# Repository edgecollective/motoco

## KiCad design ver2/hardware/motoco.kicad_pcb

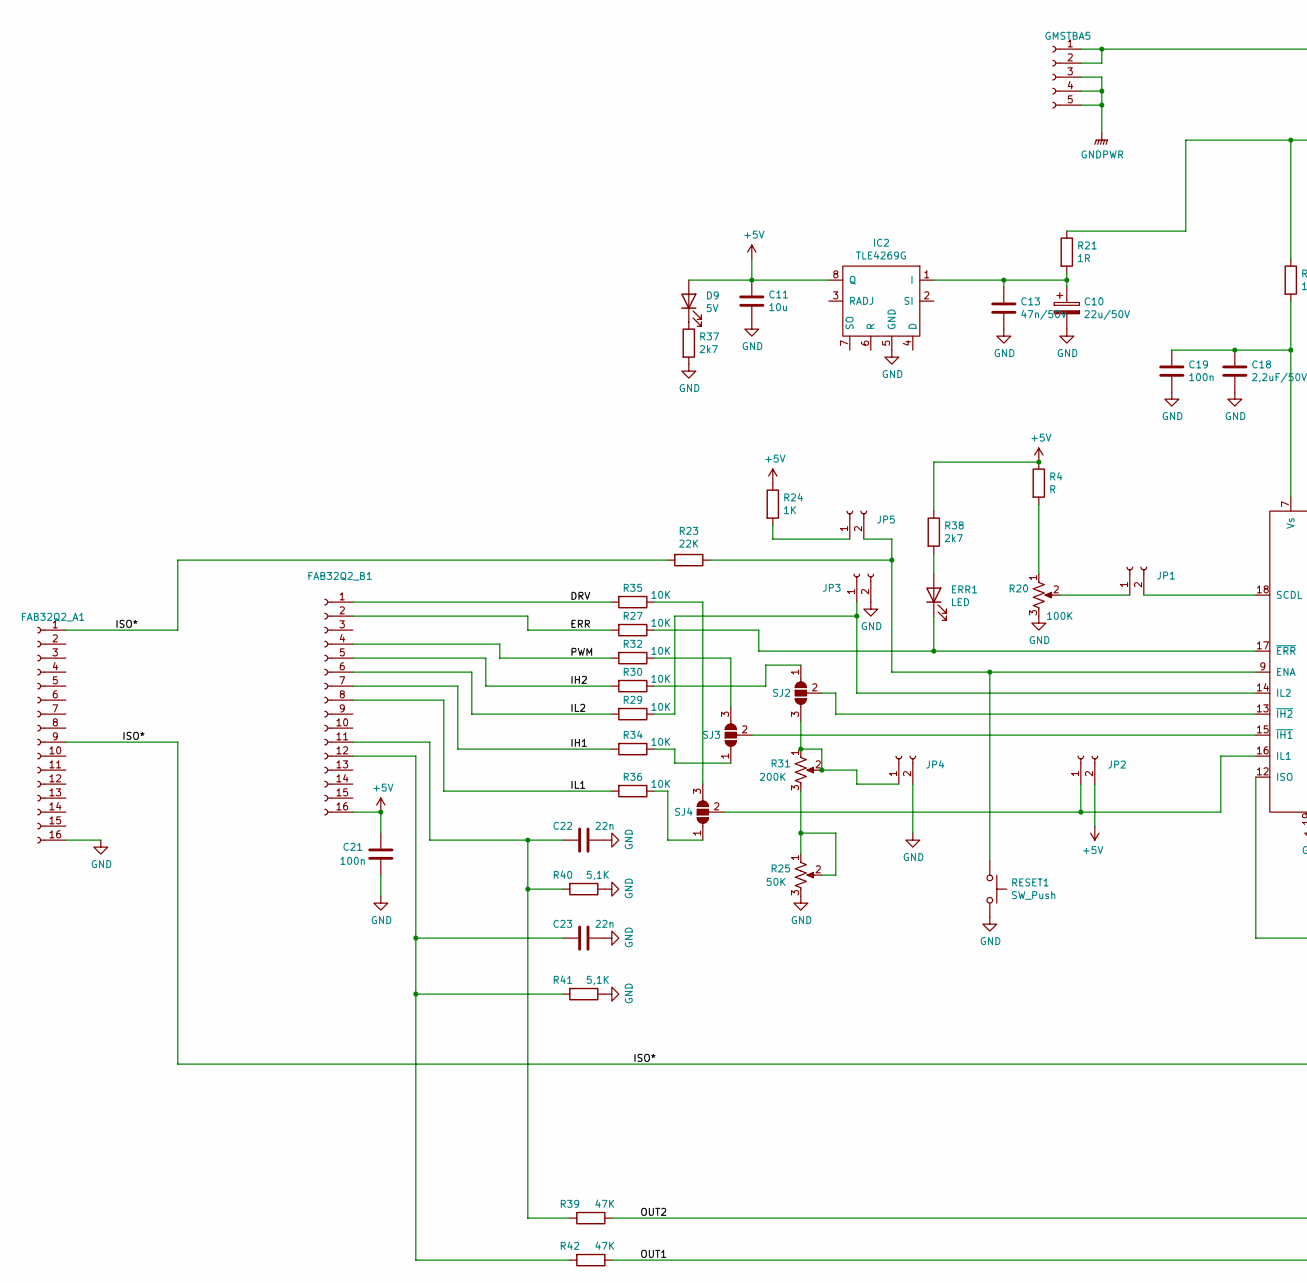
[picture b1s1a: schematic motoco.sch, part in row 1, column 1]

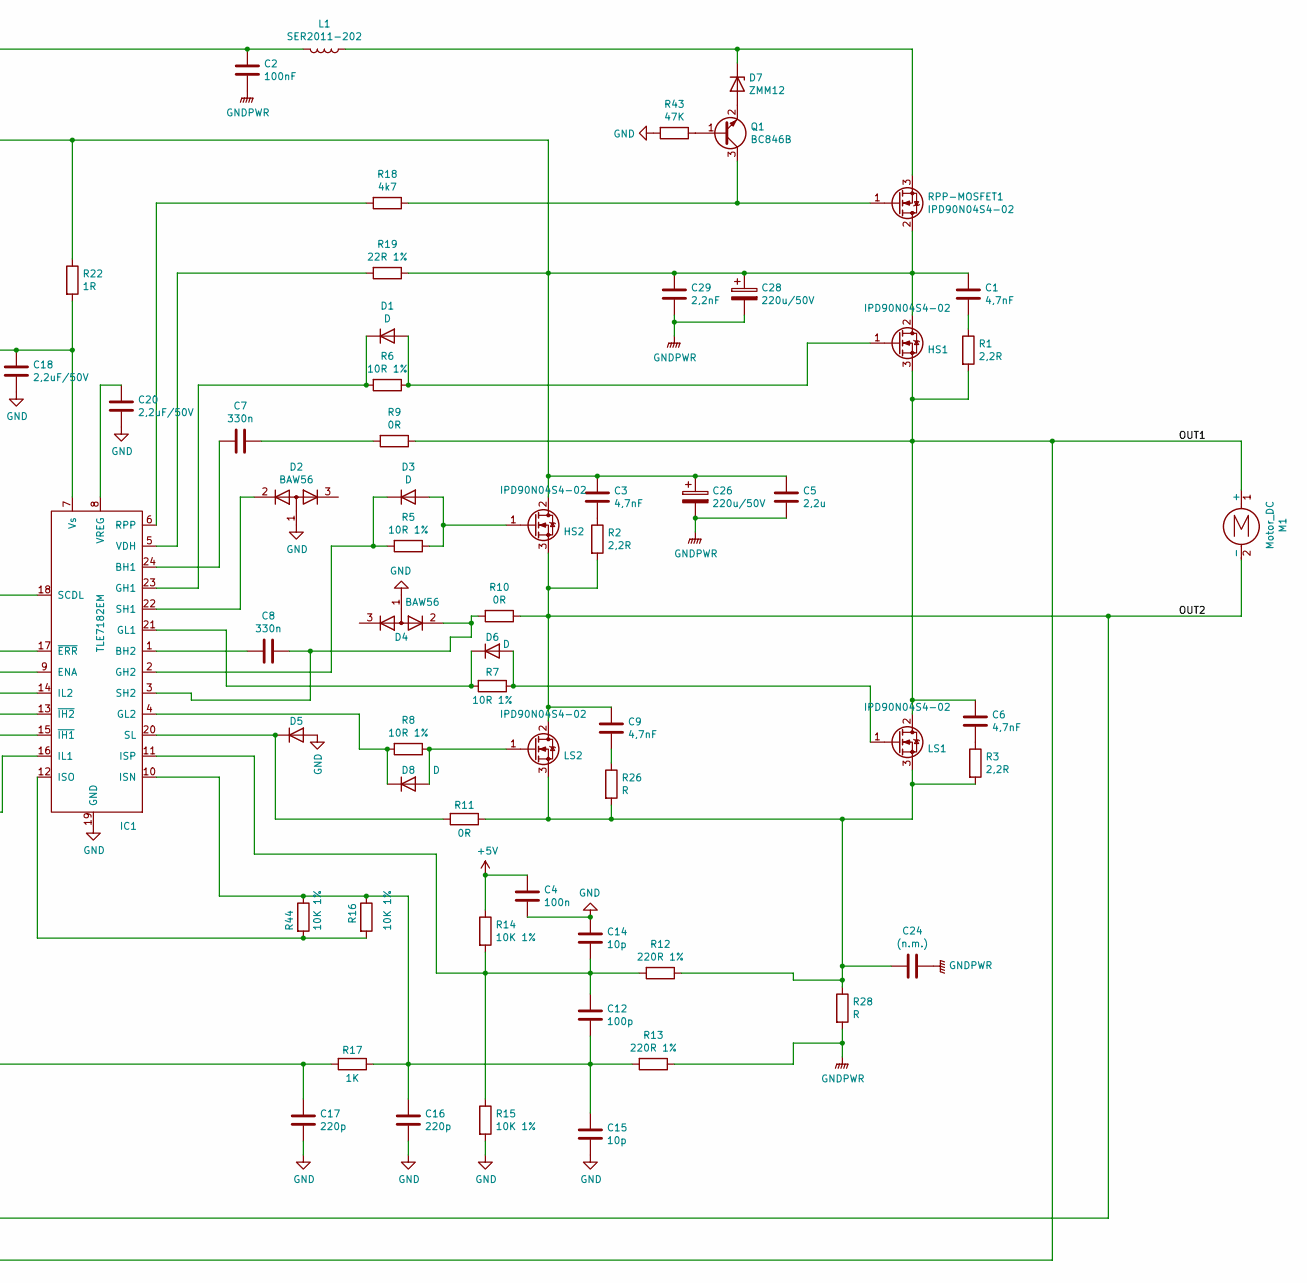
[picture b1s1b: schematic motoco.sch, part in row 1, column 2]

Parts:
C1, C3, C6, C9: 4,7nF; C_0603_1608Metric_Pad1.05x0.95mm_HandSolder
C2: 100nF; C_0603_1608Metric_Pad1.05x0.95mm_HandSolder
C4, C19, C21: 100n; C_0603_1608Metric_Pad1.05x0.95mm_HandSolder
C5: 2,2u; C_1210_3225Metric_Pad1.42x2.65mm_HandSolder
C7, C8: 330n; C_0603_1608Metric_Pad1.05x0.95mm_HandSolder
C10: 22u/50V; CP_Radial_D5.0mm_P2.00mm
C11: 10u; C_0603_1608Metric_Pad1.05x0.95mm_HandSolder
C12: 100p; C_0603_1608Metric_Pad1.05x0.95mm_HandSolder
C13: 47n/50V; C_1210_3225Metric
C14, C15: 10p; C_0603_1608Metric_Pad1.05x0.95mm_HandSolder
C16, C17: 220p; C_0603_1608Metric_Pad1.05x0.95mm_HandSolder
C18, C20: 2,2uF/50V; C_1206_3216Metric
C22, C23: 22n; C_0603_1608Metric_Pad1.05x0.95mm_HandSolder
C24: (n.m.); C_0603_1608Metric_Pad1.05x0.95mm_HandSolder
C26, C28: 220u/50V; CP_Radial_D16.0mm_P7.50mm
C29: 2,2nF; C_1210_3225Metric
D1, D3, D5, D6, D8: D; D_MiniMELF_Handsoldering
D2, D4: BAW56; SOT-23
D7: ZMM12; D_MiniMELF_Handsoldering
D9: 5V; LED_0603_1608Metric_Pad1.05x0.95mm_HandSolder
ERR1: LED; LED_0603_1608Metric_Pad1.05x0.95mm_HandSolder
FAB32Q2_A1, FAB32Q2_B1: Conn_01x16_Female; PinSocket_1x16_P2.54mm_Vertical
GMSTBA5: Conn_01x05_Female; PinSocket_1x05_P2.54mm_Vertical
HS1, HS2: IPD90N04S4-02; PG-TO-252-3-313
IC1: TLE7182EM; PG-SSOP-24-9
IC2: TLE4269G; Infineon_PG-DSO-8-43
JP1, JP2, JP3, JP4, JP5: Conn_01x02_Female; PinSocket_1x02_P2.54mm_Vertical
L1: SER2011-202; SER2011-202-REAL
LS1, LS2: IPD90N04S4-02; PG-TO-252-3-313
M1: Motor_DC; TerminalBlock_Phoenix_MKDS-1,5-2_1x02_P5.00mm_Horizontal
Q1: BC846B; SOT-23
R1, R2, R3: 2,2R; R_1206_3216Metric
R4: R; R_1206_3216Metric
R5, R6, R7, R8: 10R 1%; R_0603_1608Metric_Pad1.05x0.95mm_HandSolder
R9, R10, R11: 0R; R_0603_1608Metric_Pad1.05x0.95mm_HandSolder
R12, R13: 220R 1%; R_0603_1608Metric_Pad1.05x0.95mm_HandSolder
R14, R15, R16, R44: 10K 1%; R_0603_1608Metric_Pad1.05x0.95mm_HandSolder
R17, R24: 1K; R_0603_1608Metric_Pad1.05x0.95mm_HandSolder
R18: 4k7; R_0603_1608Metric_Pad1.05x0.95mm_HandSolder
R19: 22R 1%; R_0603_1608Metric_Pad1.05x0.95mm_HandSolder
R20: 100K; Potentiometer_Vishay_TS53YJ_Vertical
R21, R22: 1R; R_0603_1608Metric_Pad1.05x0.95mm_HandSolder
R23: 22K; R_0603_1608Metric_Pad1.05x0.95mm_HandSolder
R25: 50K; Potentiometer_Vishay_TS53YJ_Vertical
R26, R28: R; R_0603_1608Metric_Pad1.05x0.95mm_HandSolder
R27, R29, R30, R32, R34, R35, R36: 10K; R_0603_1608Metric_Pad1.05x0.95mm_HandSolder
R31: 200K; Potentiometer_Vishay_TS53YJ_Vertical
R37, R38: 2k7; R_1206_3216Metric
R39, R42, R43: 47K; R_0603_1608Metric_Pad1.05x0.95mm_HandSolder
R40, R41: 5,1K; R_0603_1608Metric_Pad1.05x0.95mm_HandSolder
RESET1: SW_Push; SW_Push_1P1T_NO_6x6mm_H9.5mm
RPP-MOSFET1: IPD90N04S4-02; PG-TO-252-3-313
SJ2, SJ3, SJ4: SolderJumper_3_Open; SolderJumper-3_P1.3mm_Open_Pad1.0x1.5mm

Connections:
+5V: C4.1, C11.2, C21.2, D9.2 (A), FAB32Q2_B1.16, IC2.8 (Q), JP2.2, R4.1, R14.1, R24.1, R38.1
/DRV: FAB32Q2_B1.1, R35.2
/ERR: FAB32Q2_B1.2, R27.2
/IH1: FAB32Q2_B1.7, R34.2
/IH2: FAB32Q2_B1.5, R30.2
/IL1: FAB32Q2_B1.8, R36.2
/IL2: FAB32Q2_B1.6, R29.2
/ISO*: C17.1, FAB32Q2_A1.1, FAB32Q2_A1.9, R17.2, R23.2
/OUT1: C6.1, HS1.3 (S), LS1.2 (D), M1.1 (+), R1.2, R9.1, R42.1
/OUT2: C9.1, HS2.3 (S), LS2.2 (D), M1.2 (-), R2.2, R10.1, R39.1
/PWM: FAB32Q2_B1.4, R32.2
GND: C4.2, C10.2, C11.1, C13.1, C14.1, C15.2, C16.2, C17.2, C18.1, C19.1, C20.1, C21.1, C22.1, C23.1, D2.1 (A), D4.1 (A), D5.2 (A), FAB32Q2_A1.16, IC1.19 (GND), IC2.5 (GND), JP3.2, JP4.2, R15.2, R20.3, R25.3, R37.2, R40.1, R41.1, R43.2, RESET1.2
GNDPWR: C2.2, C5.2, C24.1, C26.2, C28.2, C29.2, GMSTBA5.3, GMSTBA5.4, GMSTBA5.5, R13.1, R28.2
unnamed: C1.1, C3.1, C5.1, C26.1, C28.1, C29.1, HS1.2 (D), HS2.2 (D), R19.1, R21.1, R22.1, RPP-MOSFET1.2 (D)
unnamed: C1.2, R1.1
unnamed: C2.1, GMSTBA5.1, GMSTBA5.2, L1.2
unnamed: C3.2, R2.1
unnamed: C6.2, R3.1
unnamed: C7.1, R9.2
unnamed: C7.2, IC1.24 (BH1)
unnamed: C8.1, D4.2 (K), IC1.3 (SH2), R10.2
unnamed: C8.2, IC1.1 (BH2)
unnamed: C9.2, R26.1
unnamed: C10.1, C13.2, IC2.1 (I), R21.2
unnamed: C12.1, C14.2, IC1.11 (ISP), R12.2, R14.2, R15.1
unnamed: C12.2, C15.1, C16.1, IC1.10 (ISN), R13.2, R16.1, R17.1, R44.1
unnamed: C18.2, C19.2, IC1.7 (Vs), R22.2
unnamed: C20.2, IC1.8 (VREG)
unnamed: C22.2, FAB32Q2_B1.11, R39.2, R40.2
unnamed: C23.2, FAB32Q2_B1.12, R41.2, R42.2
unnamed: C24.2, LS1.3 (S), LS2.3 (S), R3.2, R11.1, R12.1, R26.2, R28.1
unnamed: D1.1 (K), IC1.23 (GH1), R6.2
unnamed: D1.2 (A), HS1.1 (G), R6.1
unnamed: D2.2 (K), IC1.22 (SH1)
unnamed: D3.1 (K), IC1.2 (GH2), R5.2
unnamed: D3.2 (A), HS2.1 (G), R5.1
unnamed: D5.1 (K), IC1.20 (SL), R11.2
unnamed: D6.1 (K), IC1.21 (GL1), R7.2
unnamed: D6.2 (A), LS1.1 (G), R7.1
unnamed: D7.1 (K), L1.1, RPP-MOSFET1.3 (S)
unnamed: D7.2 (A), Q1.2 (E)
unnamed: D8.1 (K), IC1.4 (GL2), R8.2
unnamed: D8.2 (A), LS2.1 (G), R8.1
unnamed: D9.1 (K), R37.1
unnamed: ERR1.1 (K), IC1.17 (~ERR), R27.1
unnamed: ERR1.2 (A), R38.2
unnamed: IC1.5 (VDH), R19.2
unnamed: IC1.6 (RPP), R18.2
unnamed: IC1.9 (ENA), JP5.2, R23.1, RESET1.1
unnamed: IC1.12 (ISO), R16.2, R44.2
unnamed: IC1.13 (~IH2), SJ2.2 (C)
unnamed: IC1.14 (IL2), JP3.1, R29.1
unnamed: IC1.15 (~IH1), SJ3.2 (C)
unnamed: IC1.16 (IL1), JP2.1, SJ4.2 (C)
unnamed: IC1.18 (SCDL), JP1.2
unnamed: JP1.1, R20.2
unnamed: JP4.1, R31.1, R31.2, SJ2.3 (B)
unnamed: JP5.1, R24.2
unnamed: Q1.1 (B), R43.1
unnamed: Q1.3 (C), R18.1, RPP-MOSFET1.1 (G)
unnamed: R4.2, R20.1
unnamed: R25.1, R25.2, R31.3
unnamed: R30.1, SJ2.1 (A)
unnamed: R32.1, SJ3.3 (B)
unnamed: R34.1, SJ3.1 (A)
unnamed: R35.1, SJ4.3 (B)
unnamed: R36.1, SJ4.1 (A)

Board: 2 copper layers, 102 parts (0 on the bottom side), 67 nets, no tracks yet.
